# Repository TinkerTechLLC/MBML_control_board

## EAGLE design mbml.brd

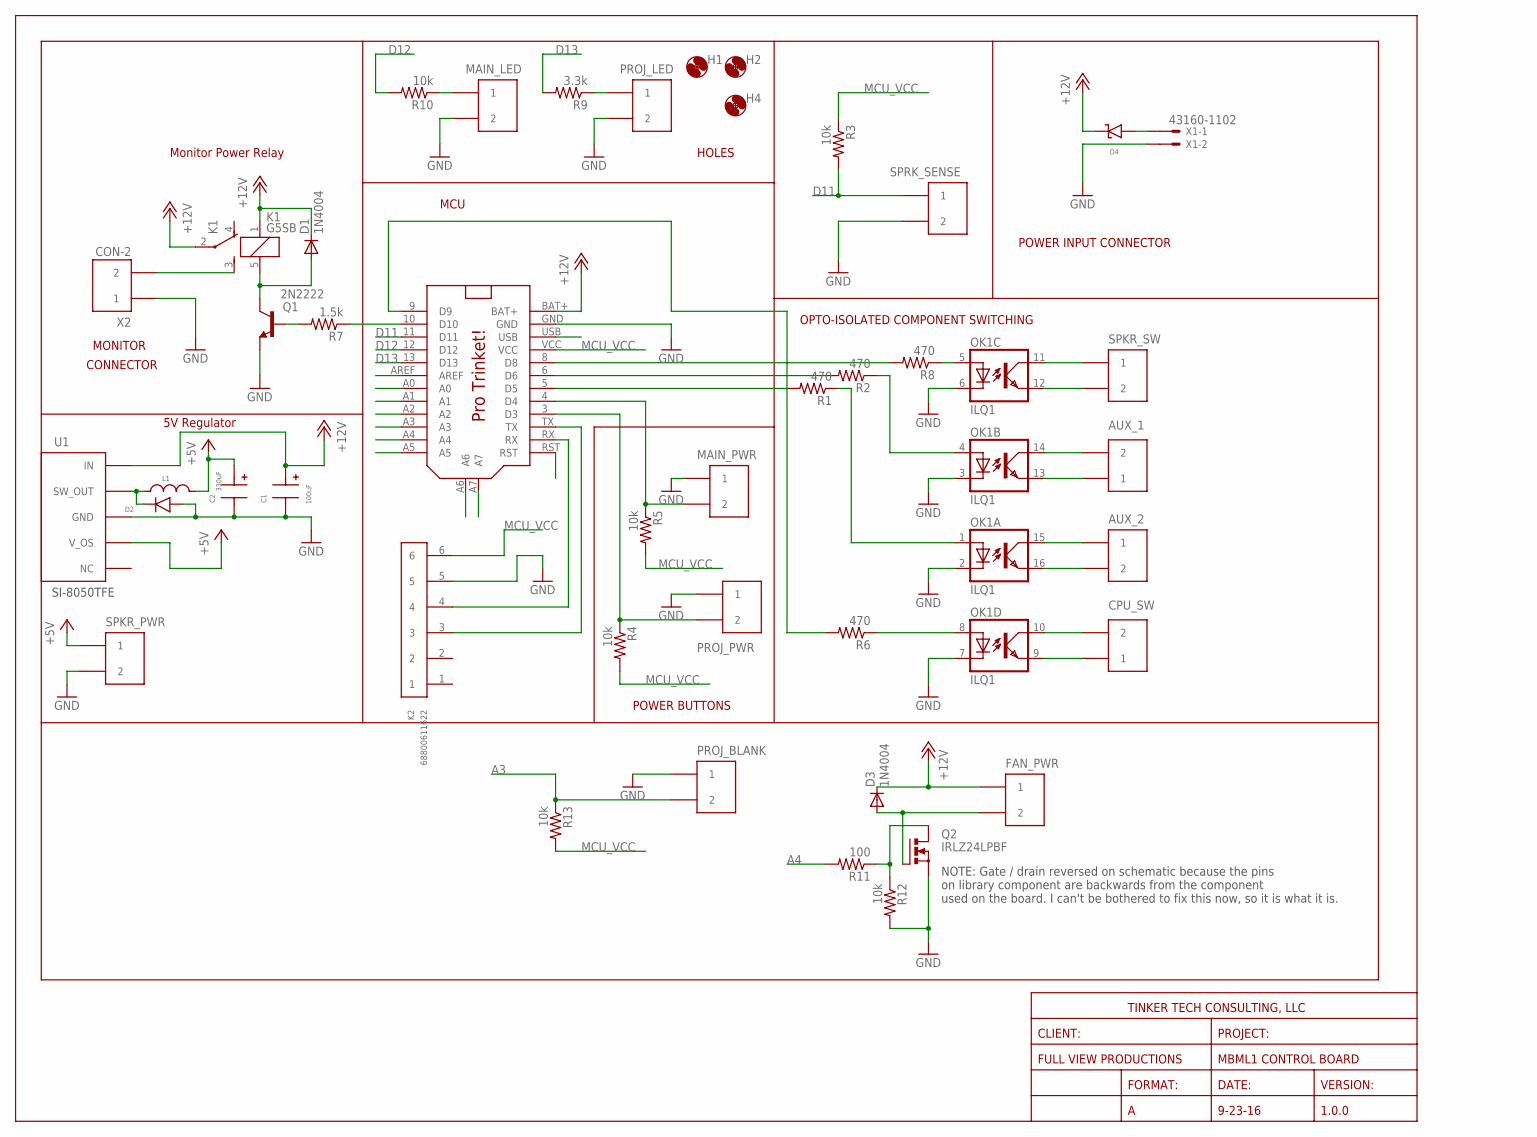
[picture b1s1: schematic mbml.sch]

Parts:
AUX_1, AUX_2: CON-2B2B-XH-A(LF)(SN); CON_2-2.5MM_TH
C1: 100uF; RADIAL_POL_6.3-DIA_2.5-SPACE
C2: 330uF; RADIAL_POL_10-DIA_5-SPACE
CPU_SW: CON-2B2B-XH-A(LF)(SN); CON_2-2.5MM_TH
D1, D3: 1N4004; DO41-10
D2: DIODE; DO-201AD_AXIAL
D4: DIODE_SHOTTKY; DO-201AD_AXIAL
FAN_PWR: CON-2B2B-XH-A(LF)(SN); CON_2-2.5MM_TH
H1, H2, H4: MOUNT-HOLE3.0; 3,0
K1: G5SB
K2: 68800611622
L1: INDUCTORRADIAL_8.5-DIA_5-SPACE; RADIAL_8.5-DIA_5-SPACE
MAIN_LED: CON-2B2B-XH-A(LF)(SN); CON_2-2.5MM_TH
MAIN_PWR: CON-2B2B-XH-A(LF)(SN); CON_2-2.5MM_TH
OK1: ILQ1; DIL16
PROJ_BLANK: CON-2B2B-XH-A(LF)(SN); CON_2-2.5MM_TH
PROJ_LED: CON-2B2B-XH-A(LF)(SN); CON_2-2.5MM_TH
PROJ_PWR: CON-2B2B-XH-A(LF)(SN); CON_2-2.5MM_TH
Q1: 2N2222; TO18
Q2: IRLZ24LPBF; TO262-V
R1, R2, R6, R8: 470; 0204/5
R3, R4, R5, R10, R12, R13: 10k; 0204/5
R7: 1.5k; 0204/5
R9: 3.3k; 0204/5
R11: 100; 0204/5
SPKR_PWR: CON-2B2B-XH-A(LF)(SN); CON_2-2.5MM_TH
SPKR_SW: CON-2B2B-XH-A(LF)(SN); CON_2-2.5MM_TH
SPRK_SENSE: CON-2B2B-XH-A(LF)(SN); CON_2-2.5MM_TH
U1: REG_5V_SWITCHING_SI-8050E; TO220F-5
U$1: PRO_TRINKET; PROTRINKET
X1: 43160-1102; 43160-XX02
X2: CON-2; MOLEX_MEGA-FIT_2

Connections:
+5V: C2.+, L1.P$2, SPKR_PWR.P$1 (1), U1.4 (V_OS)
+12V: C1.+, D1.C, D3.C, D4.-, FAN_PWR.P$1 (1), K1.1, K1.2, U1.1 (IN), U$1.BAT+
+12V_IN: D4.+, X1.1@1
A0: U$1.A0
A1: U$1.A1
A2: U$1.A2
A3: PROJ_BLANK.P$2 (2), R13.1, U$1.A3
A4: R11.2, U$1.A4
A5: U$1.A5
A6: U$1.A6
A7: U$1.A7
AREF: U$1.AREF
D3: PROJ_PWR.P$2 (2), R4.1, U$1.3 (D3)
D4: MAIN_PWR.P$2 (2), R5.1, U$1.4 (D4)
D5: R1.2, U$1.5 (D5)
D6: R2.2, U$1.6 (D6)
D9: R6.2, U$1.9 (D9)
D10: R7.1, U$1.10 (D10)
D11: R3.2, SPRK_SENSE.P$1 (1), U$1.11 (D11)
D12: R10.2, U$1.12 (D12)
D13: R9.2, U$1.13 (D13)
GND: C1.-, C2.-, D2.+, K2.5, MAIN_LED.P$2 (2), MAIN_PWR.P$1 (1), OK1.2 (C), OK1.3 (C), OK1.6 (C), OK1.7 (C), PROJ_BLANK.P$1 (1), PROJ_LED.P$2 (2), PROJ_PWR.P$1 (1), Q1.1 (E), Q2.3 (S), R12.2, SPKR_PWR.P$2 (2), SPRK_SENSE.P$2 (2), U1.3 (GND), U$1.GND, X1.2@1, X2.P$1 (1)
MCU_VCC: K2.6, R3.1, R4.2, R5.2, R13.2, U$1.VCC
MON_PWR: K1.3 (S), X2.P$2 (2)
unnamed: D2.-, L1.P$1, U1.2 (SW_OUT)
unnamed: OK1.5 (A), R8.1
unnamed: R8.2, U$1.8 (D8)
unnamed: OK1.11 (COL), SPKR_SW.P$1 (1)
unnamed: OK1.12 (EMIT), SPKR_SW.P$2 (2)
unnamed: PROJ_LED.P$1 (1), R9.1
unnamed: OK1.4 (A), R2.1
unnamed: OK1.1 (A), R1.1
unnamed: D3.A, FAN_PWR.P$2 (2), Q2.2 (G)
unnamed: Q2.1 (D), R11.1, R12.1
unnamed: MAIN_LED.P$1 (1), R10.1
unnamed: AUX_1.P$2 (2), OK1.14 (COL)
unnamed: AUX_1.P$1 (1), OK1.13 (EMIT)
unnamed: CPU_SW.P$2 (2), OK1.10 (COL)
unnamed: AUX_2.P$1 (1), OK1.15 (COL)
unnamed: AUX_2.P$2 (2), OK1.16 (EMIT)
unnamed: OK1.8 (A), R6.1
unnamed: CPU_SW.P$1 (1), OK1.9 (EMIT)
RST: U$1.RST
RX: K2.4, U$1.RX
TRANS_BASE: Q1.2 (B), R7.2
TRANS_COLLECTOR: D1.A, K1.5 (2), Q1.3 (C)
TX: K2.3, U$1.TX
USB: U$1.USB

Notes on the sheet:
MCU
HOLES
Monitor Power Relay
POWER INPUT CONNECTOR
OPTO-ISOLATED COMPONENT SWITCHING
POWER BUTTONS
FULL VIEW PRODUCTIONS
MBML1 CONTROL BOARD
PROJECT:
CLIENT:
TINKER TECH CONSULTING, LLC
VERSION:
1.0.0
DATE:
9-23-16
FORMAT:
MONITOR
CONNECTOR
5V Regulator
SI-8050TFE
NOTE: Gate / drain reversed on schematic because the pins on library component are backwards from the component used on the board. I can't be bothered to fix this now, so it is what it is.

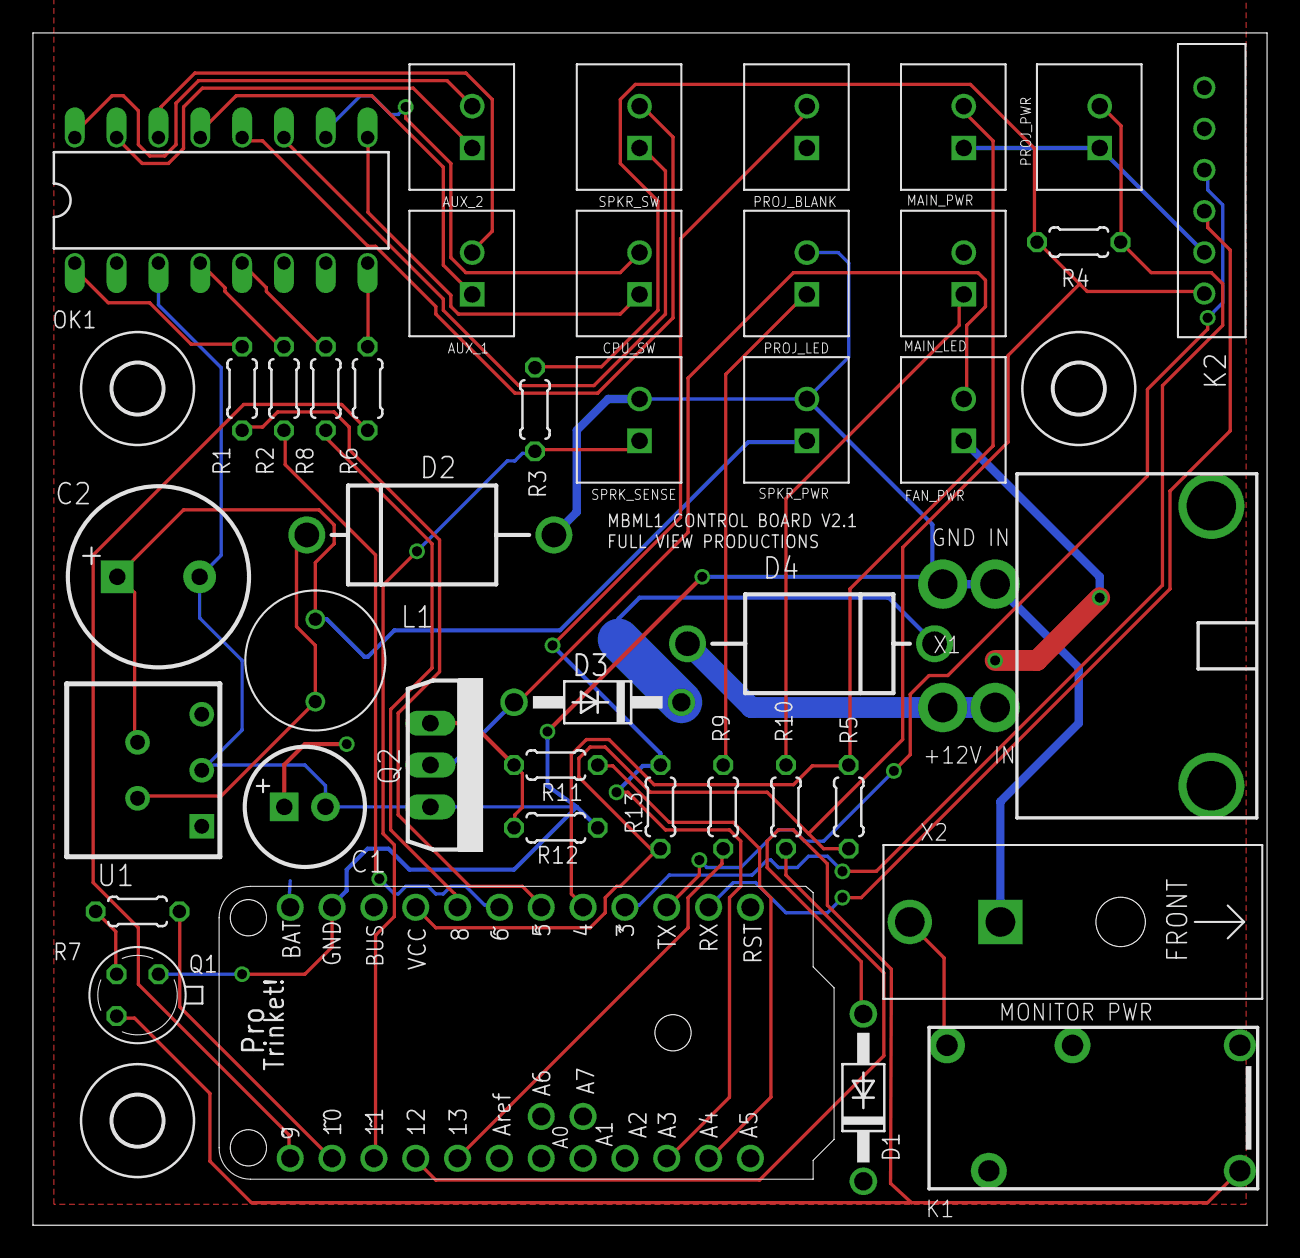
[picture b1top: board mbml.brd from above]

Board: 2 copper layers, 74.9 x 72.4 mm, 44 parts (0 on the bottom side), 39 nets.

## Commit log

2016-09-22 :tada: Added .gitattributes & .gitignore files
2016-11-22 Finished board
2017-03-24 Version 2.0 Changes
    Added:
    - 5V regulator
    - Speaker power connector
    - Fan power connector
    - Fan power photocoupler
    Fixed:
2017-03-24 Added missing resistor silkscreen name
2017-04-07 Starting major overhaul
2017-04-08 Ready for production
    Hopefully…
2017-04-08 Fixed stray unconnected trace
2017-05-08 Version 2.1, DRC OK
2017-05-08 Added reverse polarity protection
2017-05-23 Changed wire thickness
2017-06-15 Set correct values for button LED current limiting resistors
2017-07-24 MBMLV2.2
    Fixed backwards pins on fan MOSFET, added note about switching 5V
    regulator to a version that supports a higher current draw.

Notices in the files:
parts and their libraries:
Wurth_Wire_to_Board_Connectors_rev15d: Copyright: Würth Elektronik
